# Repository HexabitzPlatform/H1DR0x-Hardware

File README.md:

# H1DR0x-Hardware
Hexabitz RS232 Serial Transceiver Module Hardware Design

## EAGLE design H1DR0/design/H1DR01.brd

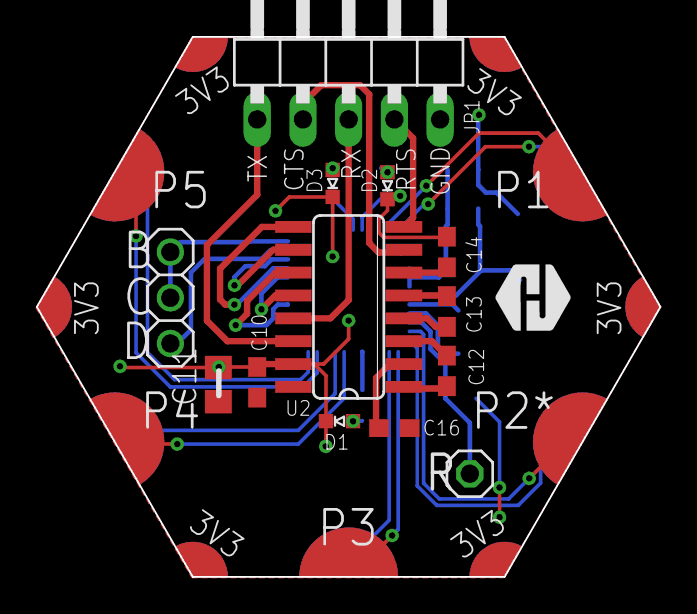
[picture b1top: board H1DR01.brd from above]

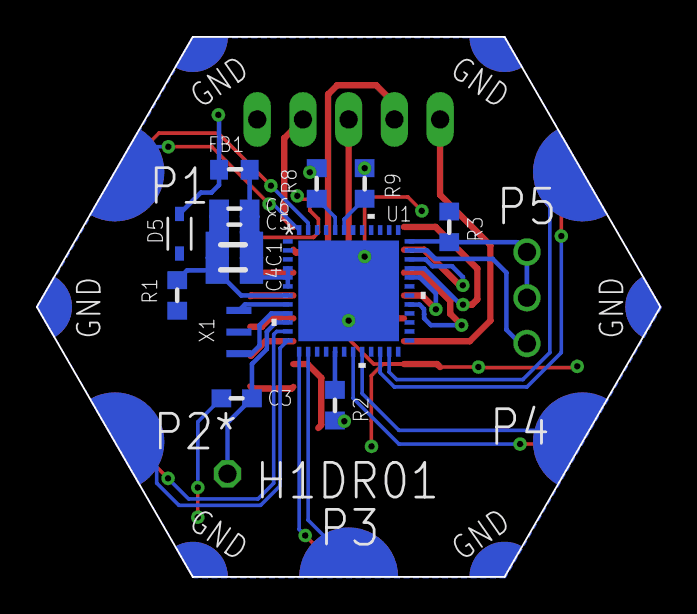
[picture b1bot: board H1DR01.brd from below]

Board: 2 copper layers, 34.6 x 30.0 mm, 29 parts (14 on the bottom side), 39 nets.

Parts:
C1: 1uF; C-0805
C3, C5, C6, C10, C12, C13, C14, C16: 100nF; C-0603
C4, C11: 4.7uF; C-0805
D1: RED; VLMS1300-GS08
D2: YELLOW; VLMS1300-GS08
D3: ORANGE; VLMS1300-GS08
D5: BOURNS_CDSOD323-T03SCBOURNS_CDSOD323-T03SC_0_0; BOURNS_CDSOD323-T03SC_0
FB1: FB-TDK_MMZ1608Y300B; FB-0603
JP1: 1X05/90
P1: HEXABIT_17.32_NO_P6
R: R; 1X01
R1: 0.0R; R-0603
R2: 270R; R-0603
R3: 10K; R-0603
R8, R9: 270.0R; R-0603
SWD: 1X03
U1: STM32G0B1CEU6QFN_B1CEU6_STM-L; QFN_B1CEU6_STM-L
U2: MAX3232CSE; SO16
U$1: HEXA-LOGO
X1: XTALL_CSTCE8M00G52

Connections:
CLK: R3.2, SWD.1, SWD.2, U1.36
CTS_OUT: JP1.2, U2.7
DATA: SWD.3, U1.35
GND: C3.2, C10.2, C11.2, C14.2, D1.C, D2.C, D3.C, D5.1, JP1.5, P1.PAD_PD7, P1.PAD_PD8, P1.PAD_PD9, P1.PAD_PD10, P1.PAD_PD11, P1.PAD_PD12, R1.1, R3.1, U1.49, U2.15, X1.P$2
unnamed: D1.A, R2.2
unnamed: R2.1, U1.17
unnamed: C3.1, R.1, U1.10
unnamed: U1.9, X1.P$1
unnamed: U1.8, X1.P$3
unnamed: R8.2, U1.44
unnamed: R9.2, U1.43
unnamed: D3.A, R9.1
unnamed: D2.A, R8.1
unnamed: C14.1, U2.6
unnamed: C16.1, U2.2
unnamed: C12.2, U2.1
unnamed: C12.1, U2.3
unnamed: C13.2, U2.4
unnamed: C13.1, U2.5
RTS_OUT: JP1.4, U2.8
RX_OUT: JP1.3, U2.13
TX_OUT: JP1.1, U2.14
UART1_CTS: U1.33, U2.9
UART1_RTS: U1.34, U2.10
UART1_RX: U1.32, U2.12
UART1_TX: U1.29, U2.11
USART2_RX: P1.PAD_PD3, U1.14
USART2_TX: P1.PAD_PU3, U1.13
USART3_RX: P1.PAD_PD5, U1.23
USART3_TX: P1.PAD_PU5, U1.22
USART4_RX: P1.PAD_PD2, U1.12
USART4_TX: P1.PAD_PU2, U1.11
USART5_RX: P1.PAD_PD4, U1.20
USART5_TX: P1.PAD_PU4, U1.19
USART6_RX: P1.PAD_PD1, U1.48
USART6_TX: P1.PAD_PU1, U1.47
VDD: C10.1, C11.1, C16.2, D5.2, FB1.2, P1.PAD_PU7, P1.PAD_PU8, P1.PAD_PU9, P1.PAD_PU10, P1.PAD_PU11, P1.PAD_PU12, U2.16
VDDA: C1.1, C4.1, C5.1, C6.1, FB1.1, U1.4, U1.5, U1.6
VSSA: C1.2, C4.2, C5.2, C6.2, R1.2, U1.7

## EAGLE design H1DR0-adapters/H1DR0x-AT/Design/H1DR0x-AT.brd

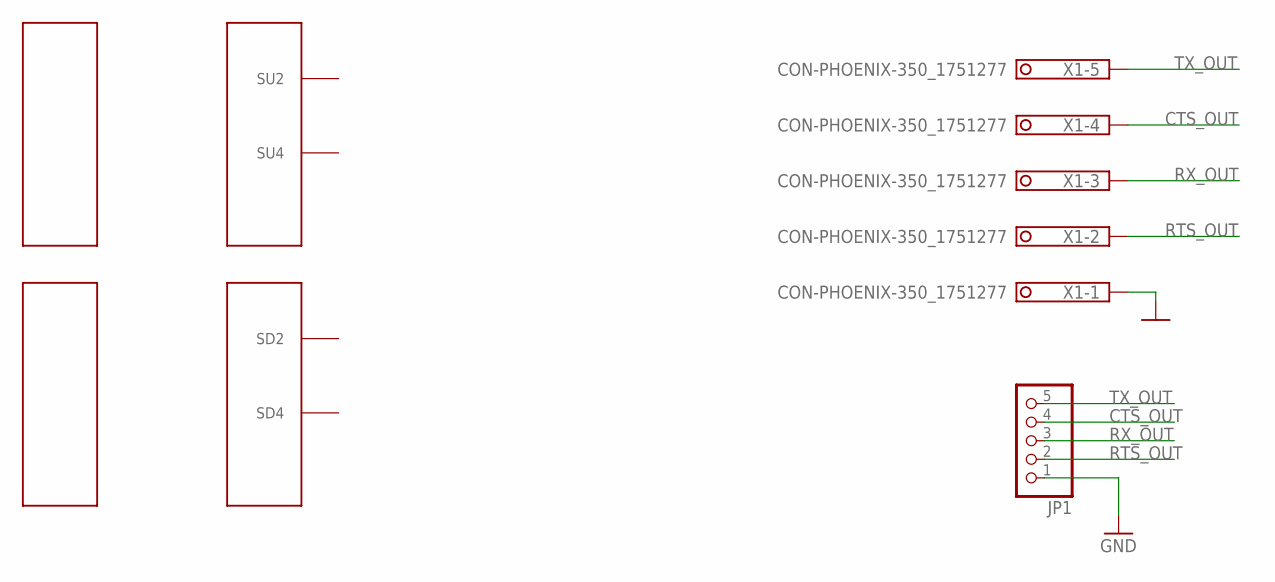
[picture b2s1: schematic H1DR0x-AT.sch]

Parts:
JP1: PINHD-1X5; F_1X05; MPN PPTC051LGBN-RC
U$1: HEXABIT_BUS_ADAPTER_WITH_PD2_PD4_PD9_PD10; HEXABIT_BUS_ADAPTER_WITH_P2_P4
X1: CON-PHOENIX-350_1751277; MPN 1751277

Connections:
CTS_OUT: JP1.4, X1.4
GND: JP1.1, X1.1
RTS_OUT: JP1.2, X1.2
RX_OUT: JP1.3, X1.3
TX_OUT: JP1.5, X1.5

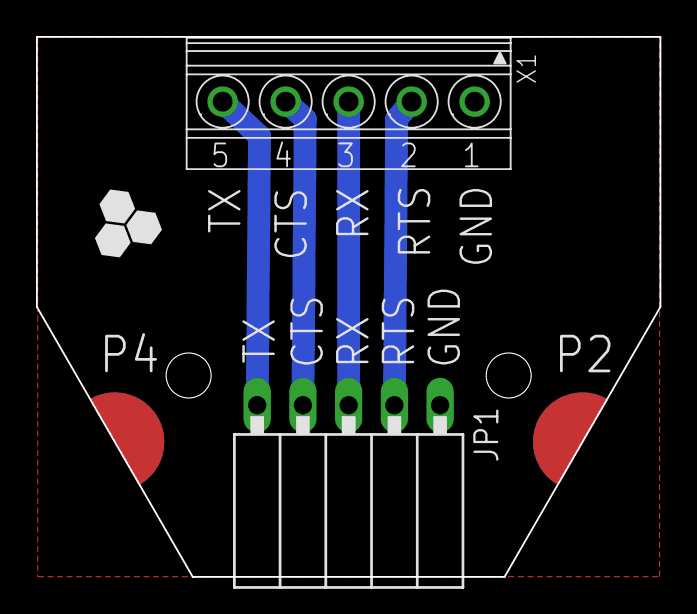
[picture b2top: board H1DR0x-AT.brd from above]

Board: 2 copper layers, 34.6 x 30.0 mm, 3 parts (0 on the bottom side), 5 nets.

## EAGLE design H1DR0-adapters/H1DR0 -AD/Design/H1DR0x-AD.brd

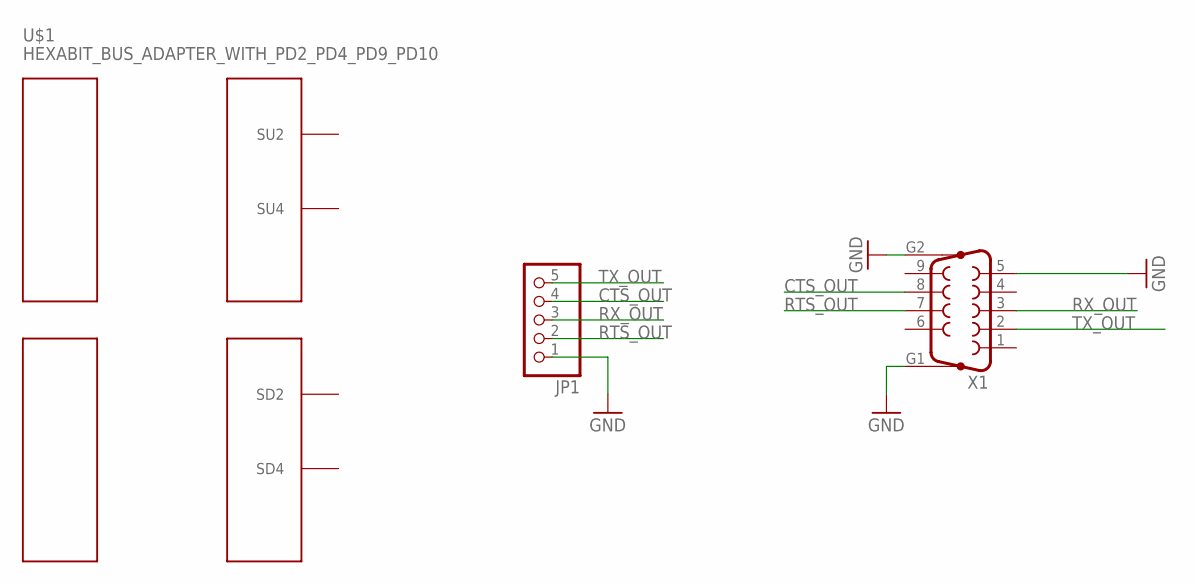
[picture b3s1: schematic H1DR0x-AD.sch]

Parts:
JP1: PINHD-1X5; F_1X05; MPN PPTC051LGBN-RC
U$1: HEXABIT_BUS_ADAPTER_WITH_PD2_PD4_PD9_PD10; HEXABIT_BUS_ADAPTER_WITH_P2_P4
X1: F09HP; MPN A-DS-09-A/KG-T2S

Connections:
CTS_OUT: JP1.4, X1.8
GND: JP1.1, X1.5, X1.G1, X1.G2
RTS_OUT: JP1.2, X1.7
RX_OUT: JP1.3, X1.3
TX_OUT: JP1.5, X1.2

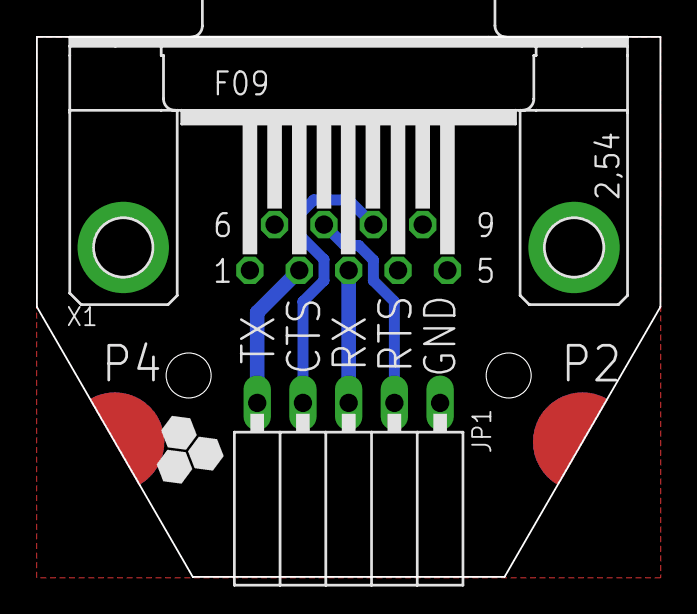
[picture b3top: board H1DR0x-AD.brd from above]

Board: 2 copper layers, 34.6 x 30.0 mm, 3 parts (0 on the bottom side), 5 nets.

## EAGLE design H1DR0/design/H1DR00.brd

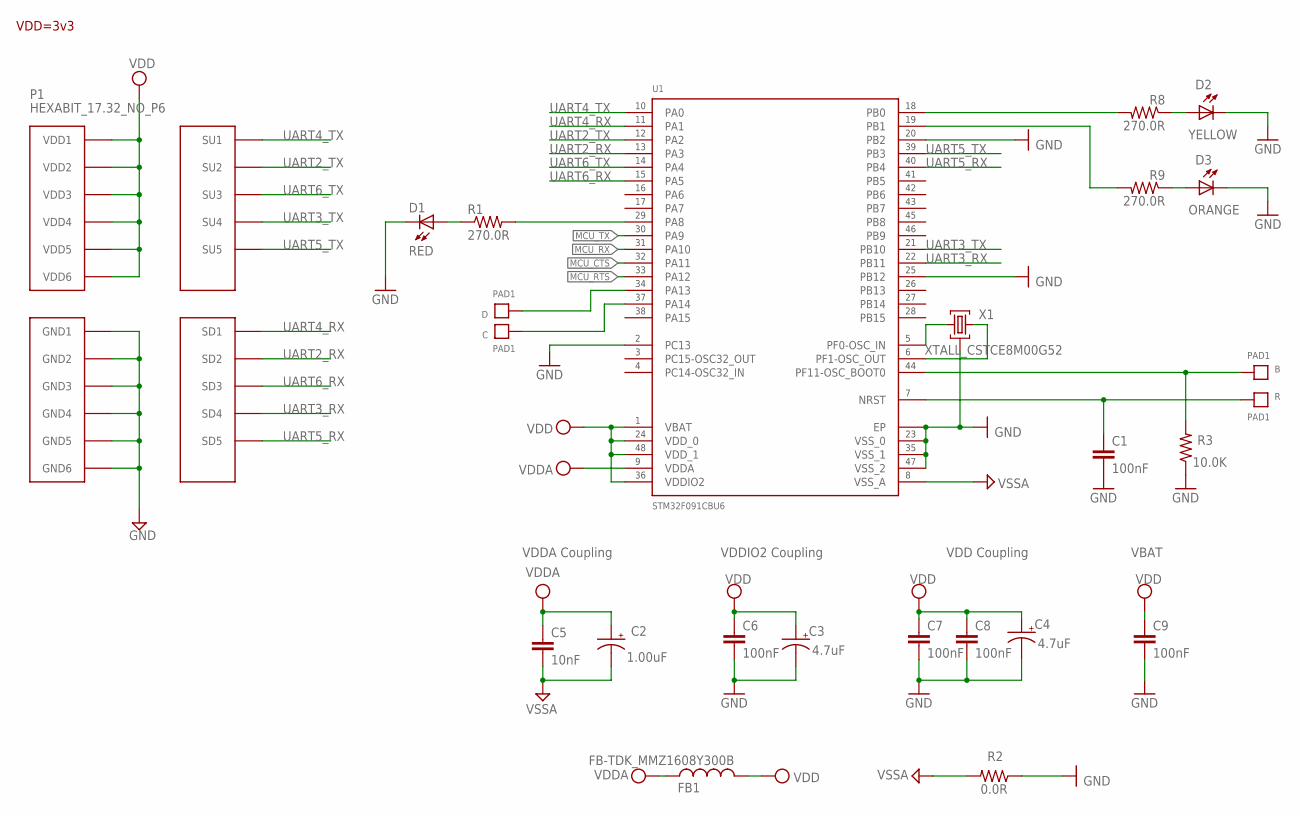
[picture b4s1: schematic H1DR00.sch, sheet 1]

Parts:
B: PAD1
C: PAD1
C1, C6, C8: 100nF; C-0603; TOLERANCE 10%; VOLTAGE_RATING 10V; MPN C0603C104K8RACTU
C2: 1.00uF; C-0805-POL; TOLERANCE 10%; VOLTAGE_RATING 16V; MPN CC0805KKX7R7BB105
C3, C4: 4.7uF; C-0805-POL; TOLERANCE 10%; VOLTAGE_RATING 25V; MPN GRM21BC81E475KA12L
C5: 10nF; C-0603; TOLERANCE 10%; VOLTAGE_RATING 50V; MPN C0603C103K5RACTU
C7: 100nF; C-0603; TOLERANCE 10%; VOLTAGE_RATING 10; MPN C0603C104K8RACTU
C9: 100nF; C-0603; TOLERANCE 10V; VOLTAGE_RATING 10%; MPN C0603C104K8RACTU
D: PAD1
D1: RED; VLMS1300-GS08; MPN VLMS1300-GS08
D2: YELLOW; VLMS1300-GS08; MPN VLMY1300-GS08
D3: ORANGE; VLMS1300-GS08; MPN VLMO1300-GS08
FB1: FB-TDK_MMZ1608Y300B; MPN MMZ1608Y300B
P1: HEXABIT_17.32_NO_P6
R: PAD1
R1, R8, R9: 270.0R; R-0603; TOLERANCE 1%; MPN RC0603FR-07270RL
R2: 0.0R; R-0603; MPN RC0603JR-070RL
R3: 10.0K; R-0603; TOLERANCE 5%; MPN RC0603JR-0710KL
U1: STM32F091CBU6
X1: XTALL_CSTCE8M00G52

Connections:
B1: B.P$1, B.P$2, R3.2, U1.P$44 (PF11-OSC_BOOT0)
GND: C1.2, C3.2 (-), C4.2 (-), C6.2, C7.2, C8.2, C9.2, D1.C, D2.C, D3.C, P1.PAD_PD7 (GND1), P1.PAD_PD8 (GND2), P1.PAD_PD9 (GND3), P1.PAD_PD10 (GND4), P1.PAD_PD11 (GND5), P1.PAD_PD12 (GND6), R2.1, R3.1, U1.EP, U1.P$2 (PC13), U1.P$20 (PB2), U1.P$23 (VSS_0), U1.P$25 (PB12), U1.P$35 (VSS_1), U1.P$47 (VSS_2), X1.P$2 (2); also elsewhere on the board
MCU_CTS: U1.P$32 (PA11); also elsewhere on the board
MCU_RTS: U1.P$33 (PA12); also elsewhere on the board
MCU_RX: U1.P$31 (PA10); also elsewhere on the board
MCU_TX: U1.P$30 (PA9); also elsewhere on the board
unnamed: D.P$1, D.P$2, U1.P$34 (PA13)
unnamed: R1.2, U1.P$29 (PA8)
unnamed: D1.A, R1.1
unnamed: U1.P$5 (PF0-OSC_IN), X1.P$1 (1)
unnamed: U1.P$6 (PF1-OSC_OUT), X1.P$3 (3)
unnamed: C.P$1, C.P$2, U1.P$37 (PA14)
unnamed: R8.2, U1.P$18 (PB0)
unnamed: D2.A, R8.1
unnamed: R9.2, U1.P$19 (PB1)
unnamed: D3.A, R9.1
R1: C1.1, R.P$1, R.P$2, U1.P$7 (NRST)
UART2_RX: P1.PAD_PD2 (SD2), U1.P$13 (PA3)
UART2_TX: P1.PAD_PU2 (SU2), U1.P$12 (PA2)
UART3_RX: P1.PAD_PD4 (SD4), U1.P$22 (PB11)
UART3_TX: P1.PAD_PU4 (SU4), U1.P$21 (PB10)
UART4_RX: P1.PAD_PD1 (SD1), U1.P$11 (PA1)
UART4_TX: P1.PAD_PU1 (SU1), U1.P$10 (PA0)
UART5_RX: P1.PAD_PD5 (SD5), U1.P$40 (PB4)
UART5_TX: P1.PAD_PU5 (SU5), U1.P$39 (PB3)
UART6_RX: P1.PAD_PD3 (SD3), U1.P$15 (PA5)
UART6_TX: P1.PAD_PU3 (SU3), U1.P$14 (PA4)
VDD: C3.1 (+), C4.1 (+), C6.1, C7.1, C8.1, C9.1, FB1.2, P1.PAD_PU7 (VDD1), P1.PAD_PU8 (VDD2), P1.PAD_PU9 (VDD3), P1.PAD_PU10 (VDD4), P1.PAD_PU11 (VDD5), P1.PAD_PU12 (VDD6), U1.P$1 (VBAT), U1.P$24 (VDD_0), U1.P$36 (VDDIO2), U1.P$48 (VDD_1); also elsewhere on the board
VDDA: C2.1 (+), C5.1, FB1.1, U1.P$9 (VDDA)
VSSA: C2.2 (-), C5.2, R2.2, U1.P$8 (VSS_A)

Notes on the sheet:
VDDA Coupling
VDDIO2 Coupling
VDD Coupling
VBAT
VDD=3v3

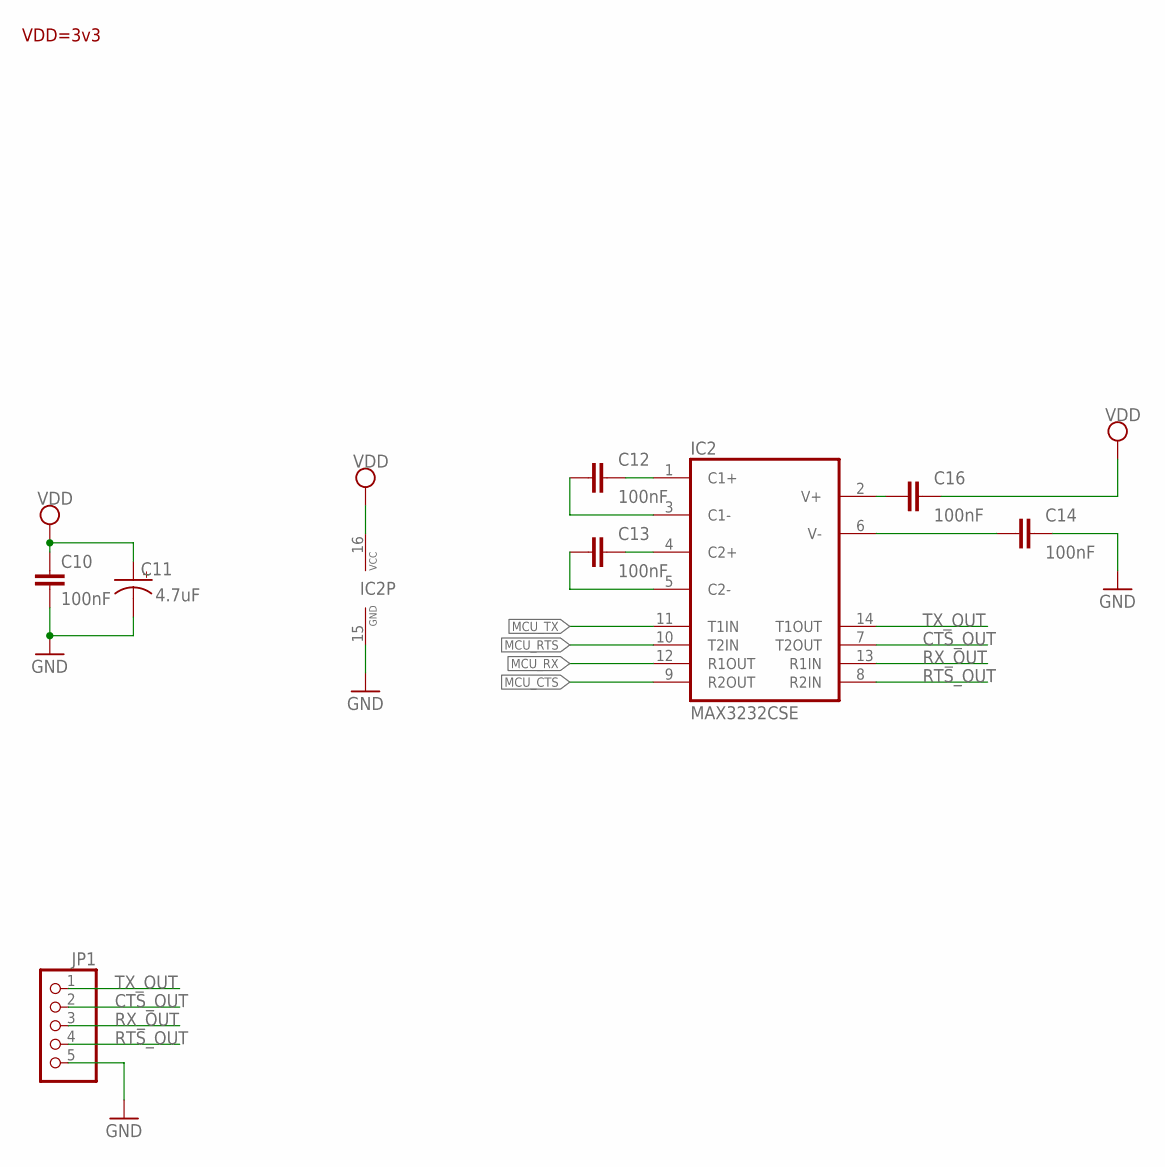
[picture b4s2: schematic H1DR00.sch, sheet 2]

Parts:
C10: 100nF; C-0603; TOLERANCE 10%; VOLTAGE_RATING 10V; MPN C0603C104K8RACTU
C11: 4.7uF; C-0805-POL; TOLERANCE 10%; VOLTAGE_RATING 25V; MPN GRM21BC81E475KA12L
C12, C13, C14, C16: 100nF; C-0603; TOLERANCE 10%; VOLTAGE_RATING 10; MPN C0603C104K8RACTU
IC2: MAX3232CSE; SO16
JP1: PINHD-1X5/90; 1X05/90

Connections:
CTS_OUT: IC2.7 (T2OUT), JP1.2
GND: C10.2, C11.2 (-), C14.2, IC2.15 (GND), JP1.5; also elsewhere on the board
MCU_CTS: IC2.9 (R2OUT); also elsewhere on the board
MCU_RTS: IC2.10 (T2IN); also elsewhere on the board
MCU_RX: IC2.12 (R1OUT); also elsewhere on the board
MCU_TX: IC2.11 (T1IN); also elsewhere on the board
unnamed: C14.1, IC2.6 (V-)
unnamed: C16.1, IC2.2 (V+)
unnamed: C12.2, IC2.1 (C1+)
unnamed: C12.1, IC2.3 (C1-)
unnamed: C13.2, IC2.4 (C2+)
unnamed: C13.1, IC2.5 (C2-)
RTS_OUT: IC2.8 (R2IN), JP1.4
RX_OUT: IC2.13 (R1IN), JP1.3
TX_OUT: IC2.14 (T1OUT), JP1.1
VDD: C10.1, C11.1 (+), C16.2, IC2.16 (VCC); also elsewhere on the board

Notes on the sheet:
VDD=3v3

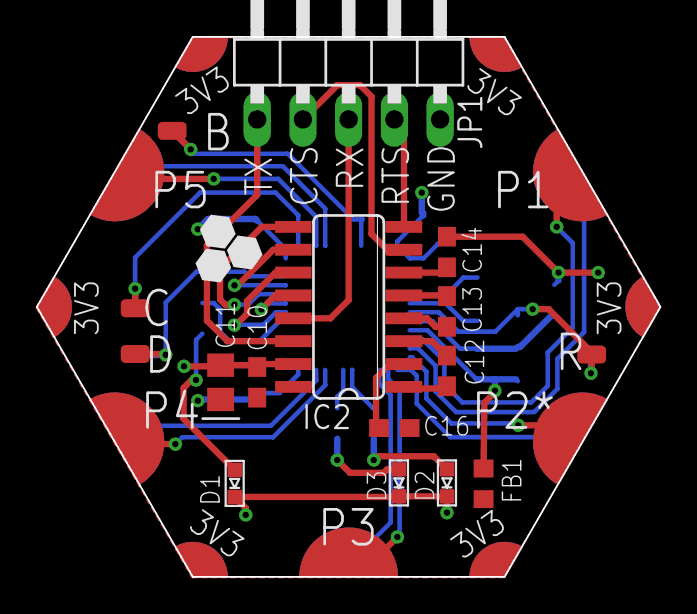
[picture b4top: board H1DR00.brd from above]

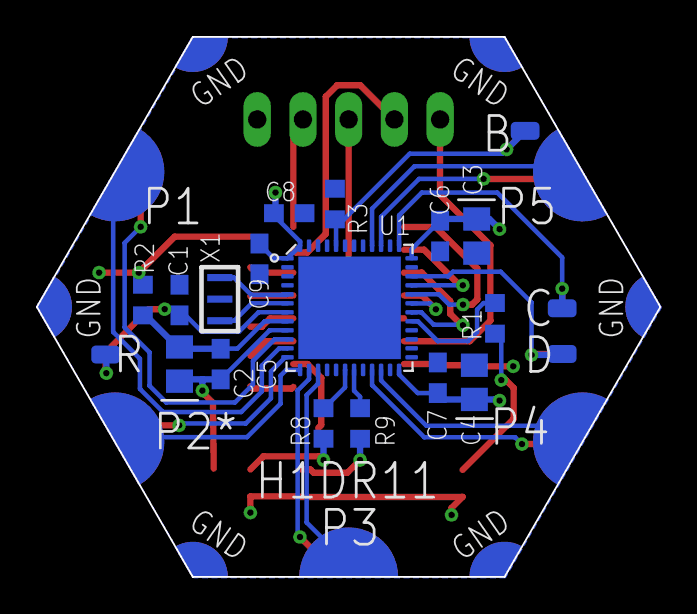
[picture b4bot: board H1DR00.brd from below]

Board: 2 copper layers, 34.6 x 30.0 mm, 33 parts (16 on the bottom side), 40 nets.

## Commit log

2020-04-19 final un-checked module
2020-04-25 add DB9 adapter module
2020-04-26 no message
2020-04-26 logo & PN were added
2020-04-26 5 way terminal block adapter module
2020-05-28 OUTPUT CAM files generated
2020-06-14 Rename folder Generate sch PDF Release module and adapters at Rev 0
2020-08-14 Update PN to H1DR01
2024-12-03 Changed cpu to G0 - New schematic. - New layout. - Generated documentation. - Generated BOM.
2024-12-11 - Deleted unnecessary files
2024-12-11 Revert "- Deleted unnecessary files"
    This reverts commit 4d997dbe3c8c92e299438b4b88b94f55f51ad360.
2024-12-12 - Fixed layout - Fixed descriptions in BOM
2024-12-14 - Changed logo in layout - Rearranged components in BOM

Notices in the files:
parts and their libraries:
COPYRIGHT: Copyright (C) 2021 Ultra Librarian. All rights reserved.
